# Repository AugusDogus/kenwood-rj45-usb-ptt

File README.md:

# kenwood-rj45-usb-ptt

USB push-to-talk adapter for Kenwood-style RJ45 handheld microphones such as KMC-30 / KMC-32 compatible mics.

## Why

The goal is a CB-radio-style handheld PTT mic for a computer, and nothing off the shelf does the whole job. USB PTT mics are desktop/gooseneck units, handheld dispatch mics with the right feel are not USB (XLR, RJ45, or radio-specific plugs) and need extra hardware, and USB handheld mics have no PTT switch. Level-triggered or software PTT is unreliable; the mic's physical switch should be the trigger.

This adapter closes that gap: plug in a cheap, widely available Kenwood-style RJ45 hand mic and the board shows up as a standard USB audio microphone plus a USB HID keyboard that holds F13 while PTT is pressed, so any app with a push-to-talk keybind (Discord, Mumble, dispatch software) works with no drivers or custom software.

Rev A is a PCBWay-assemblable board. It uses a Seeed XIAO RP2040 module for USB and firmware, an MCP6002 analog front-end for the microphone, and an RJ45 jack for the hand mic.

## What To Upload To PCBWay

Use the release assets from `v0.1.0`, or the matching files in `manufacturing/revA/`:

- `kenwood-rj45-usb-ptt-revA-fabrication.zip` for PCB fabrication Gerbers/drill
- `BOM_pcbway_revA.csv` for assembly BOM
- `positions_revA.csv` for pick-and-place / centroid
- `PCBWAY_NOTES_revA.md` for assembly notes

`manufacturing/revA/ORDER_INSTRUCTIONS.md` has the same checklist in upload order.

## Current Status

- KiCad DRC: 0 violations
- Unconnected items: 0
- Firmware: not implemented yet
- First hardware spin: order a small quantity only

## Repository Layout

- `hardware/kicad/` - KiCad 9 project, board, schematic, and vendored footprint/symbol libraries
- `manufacturing/revA/` - PCBWay-ready fabrication and assembly outputs
- `firmware/` - firmware plan and future XIAO RP2040 code
- `tools/` - board generation helper used for Rev A
- `docs/` - design/order notes

## Rev A Architecture

```text
Kenwood RJ45 hand mic
  mic audio -> electret bias -> MCP6002 preamp -> XIAO RP2040 ADC -> USB audio microphone
  PTT       -> debounced GPIO -> XIAO RP2040 USB HID keyboard -> F13 while held

Computer USB-C -> exposed USB-C connector on Seeed XIAO RP2040 module
```

RJ45 pin 2 is intentionally left open. Some Kenwood-style radios provide accessory power on that pin, but Rev A does not feed voltage into it.

## Open In KiCad

Open:

`hardware/kicad/radio-mic-usb-ptt.kicad_pro`

The KiCad project uses project-relative library tables, so it should open from this repo without global library setup.

## Regenerate Rev A Board

The final board file is already generated and routed. To regenerate the unrouted board from the helper script:

```sh
NO_ROUTES=1 python3 tools/generate_revA_board.py
```

Then autoroute/import in KiCad or with the MCP tooling. Do not run multi-attempt autorouting unless you explicitly want multiple confirmation prompts.

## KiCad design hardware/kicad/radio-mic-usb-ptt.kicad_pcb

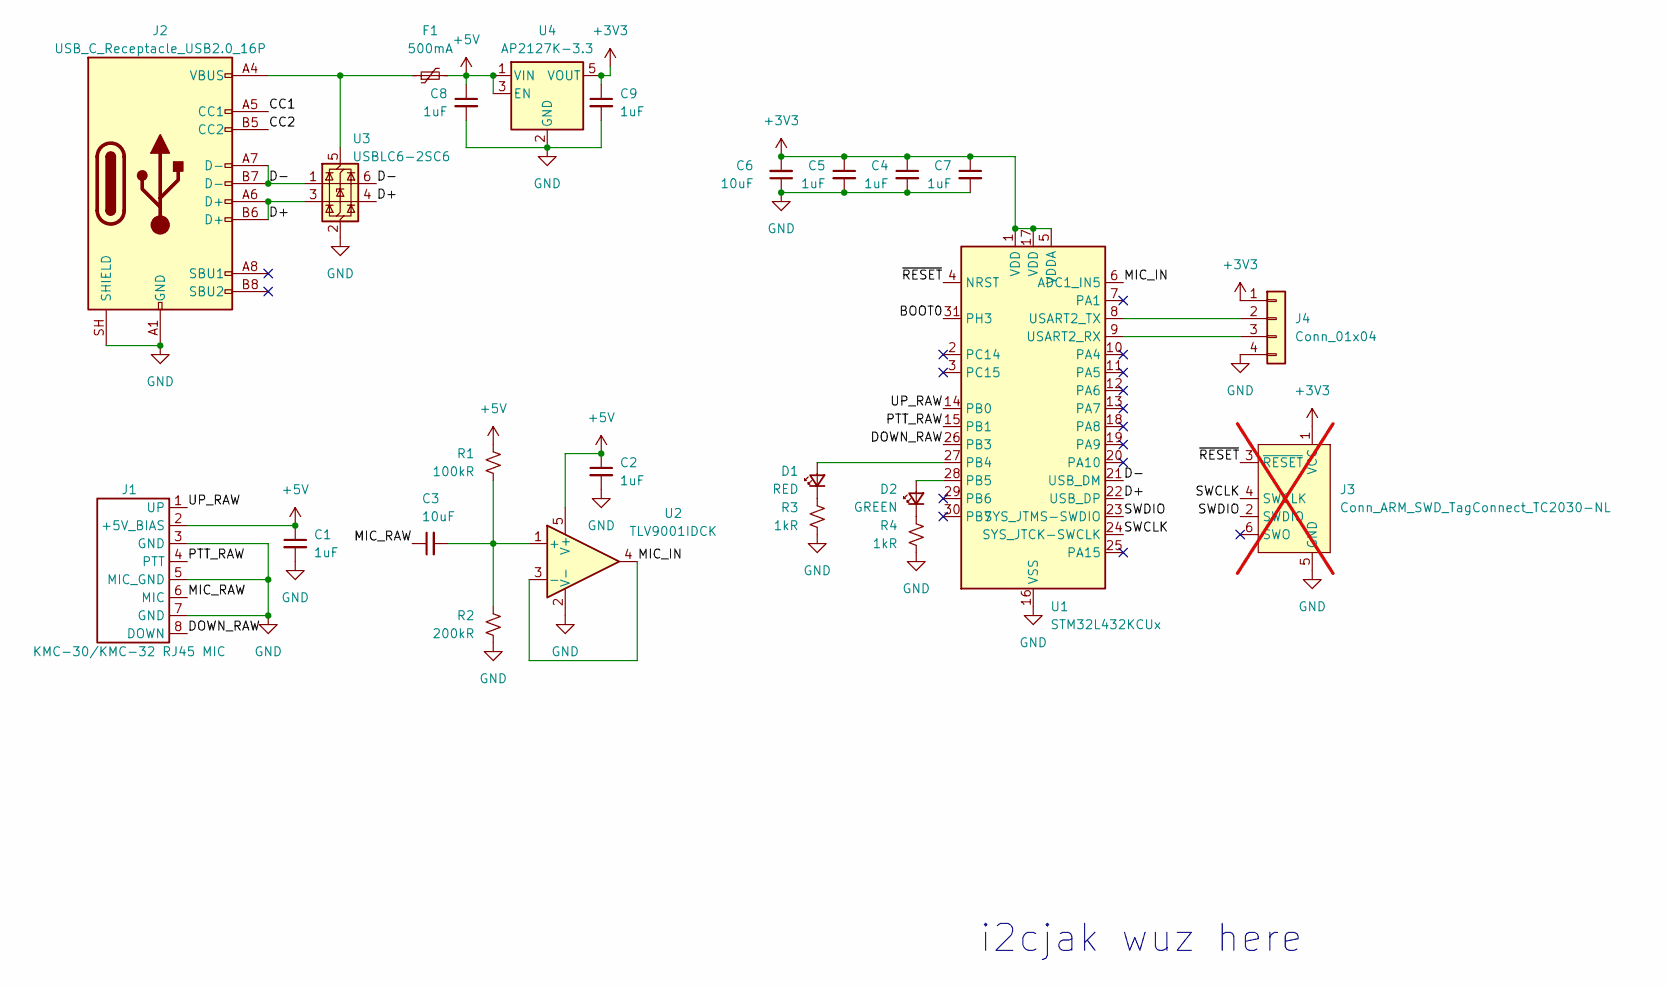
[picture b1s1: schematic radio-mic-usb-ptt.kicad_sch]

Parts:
C1, C2, C4, C5, C7, C8, C9: 1uF; C_0603_1608Metric
C3, C6: 10uF; C_0603_1608Metric
D1: RED; D_0603_1608Metric
D2: GREEN; D_0603_1608Metric
F1: 500mA; Fuse_0805_2012Metric
J1: KMC-30/KMC-32 RJ45 MIC; RJ45_Amphenol_RJHSE5380
J2: USB_C_Receptacle_USB2.0_16P; USB_C_Receptacle_HRO_TYPE-C-31-M-12
J3: Conn_ARM_SWD_TagConnect_TC2030-NL; Tag-Connect_TC2030-IDC-NL_2x03_P1.27mm_Vertical; not fitted
J4: Conn_01x04; PinHeader_1x04_P2.54mm_Vertical
R1: 100kR; R_0603_1608Metric
R2: 200kR; R_0603_1608Metric
R3, R4: 1kR; R_0603_1608Metric
U1: STM32L432KCUx; QFN-32-1EP_5x5mm_P0.5mm_EP3.45x3.45mm
U2: TLV9001IDCK; SOT-353_SC-70-5
U3: USBLC6-2SC6; SOT-23-6
U4: AP2127K-3.3; SOT-23-5

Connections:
+3V3: C4.1, C5.1, C6.2, C7.1, C9.1, J3.1 (VCC), J4.1, U1.1 (VDD), U1.5 (VDDA), U1.17 (VDD), U4.5 (VOUT)
+5V: C1.1, C2.1, C8.1, F1.2, J1.2 (+5V_BIAS), R1.1, U2.5 (V+), U4.1 (VIN), U4.3 (EN)
/BOOT0: U1.31 (PH3)
/CC1: J2.A5 (CC1)
/CC2: J2.B5 (CC2)
/D+: J2.A6 (D+), J2.B6 (D+), U1.22 (USB_DP), U3.3 (I/O2), U3.4 (I/O2)
/D-: J2.A7 (D-), J2.B7 (D-), U1.21 (USB_DM), U3.1 (I/O1), U3.6 (I/O1)
/DOWN_RAW: J1.8 (DOWN), U1.26 (PB3)
/MIC_IN: U1.6 (ADC1_IN5), U2.3 (-), U2.4
/MIC_RAW: C3.1, J1.6 (MIC)
/PTT_RAW: J1.4 (PTT), U1.15 (PB1)
/SWCLK: J3.4 (SWCLK), U1.24 (SYS_JTCK-SWCLK)
/SWDIO: J3.2 (SWDIO), U1.23 (SYS_JTMS-SWDIO)
/UP_RAW: J1.1 (UP), U1.14 (PB0)
/~RESET: J3.3 (~RESET), U1.4 (NRST)
GND: C1.2, C2.2, C4.2, C5.2, C6.1, C7.2, C8.2, C9.2, J1.3 (GND), J1.5 (MIC_GND), J1.7 (GND), J2.A1 (GND), J2.A12 (GND), J2.B1 (GND), J2.B12 (GND), J2.SH (SHIELD), J3.5 (GND), J4.4, R2.2, R3.2, R4.2, U1.16 (VSS), U1.32 (VSS), U1.33 (VSS), U2.2 (V-), U3.2 (GND), U4.2 (GND)
unnamed: D1.2 (A), U1.27 (PB4)
unnamed: D1.1 (K), R3.1
unnamed: D2.2 (A), U1.28 (PB5)
unnamed: D2.1 (K), R4.1
unnamed: J4.2, U1.8 (USART2_TX)
unnamed: J4.3, U1.9 (USART2_RX)
unnamed: C3.2, R1.2, R2.1, U2.1 (+)
unnamed: F1.1, J2.A4 (VBUS), J2.A9 (VBUS), J2.B4 (VBUS), J2.B9 (VBUS), U3.5 (VBUS)

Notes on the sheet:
i2cjak wuz here

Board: 2 copper layers, 24 parts (1 on the bottom side), 21 nets, no tracks yet.

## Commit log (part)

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2026-06-26 Add Rev A USB PTT hardware design
2026-06-26 Rename README project title
2026-06-26 Split Rev A release assets
